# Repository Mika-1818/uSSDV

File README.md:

# uSSDV
µSSDV is a gps tracker and image transmission system built on the cheap esp32 cam module.
This is still work in progress and not tested yet. Expect to see some tests soon though.

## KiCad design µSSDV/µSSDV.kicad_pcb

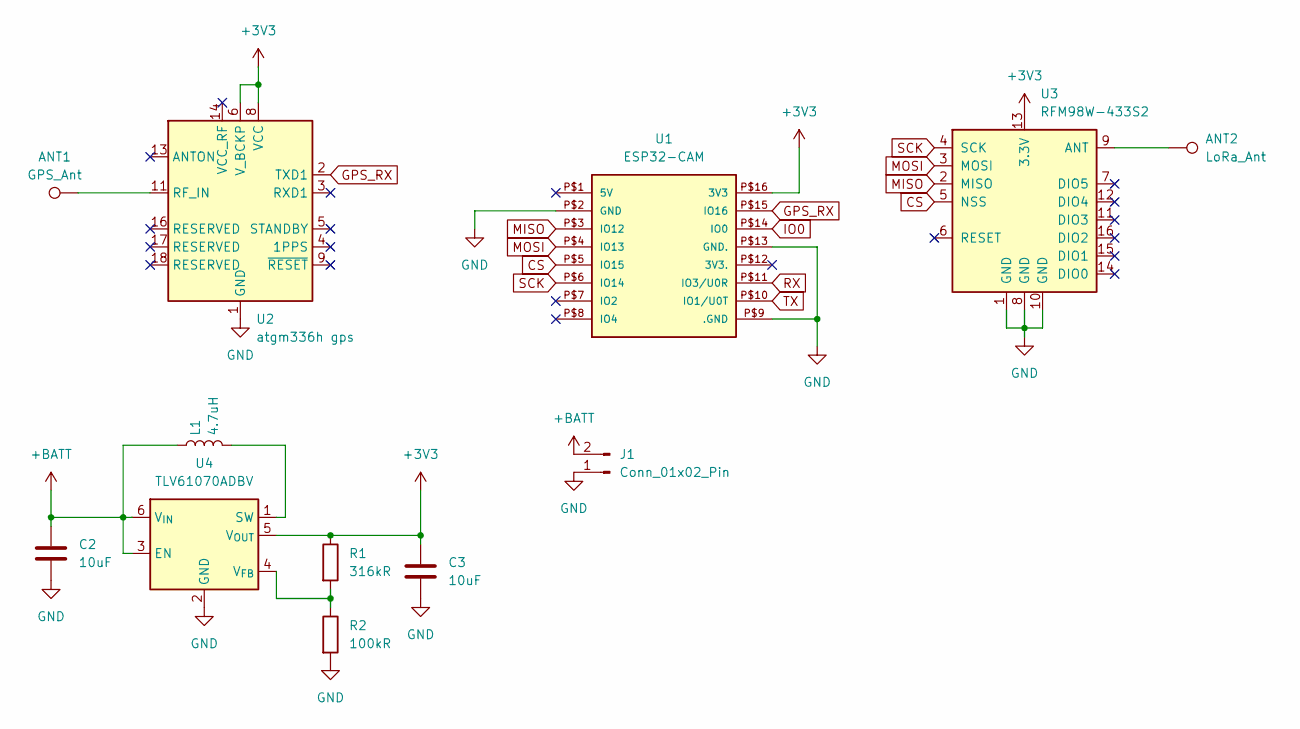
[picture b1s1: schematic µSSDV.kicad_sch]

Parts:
ANT1: GPS_Ant; PinHeader_1x01_P2.54mm_Vertical
ANT2: LoRa_Ant; PinHeader_1x01_P2.54mm_Vertical
C2, C3: 10uF; C_0603_1608Metric_Pad1.08x0.95mm_HandSolder
J1: Conn_01x02_Pin; PinHeader_1x02_P2.54mm_Vertical
L1: 4.7uH; L_Changjiang_FNR5040S
R1: 316kR; R_0603_1608Metric_Pad0.98x0.95mm_HandSolder
R2: 100kR; R_0603_1608Metric_Pad0.98x0.95mm_HandSolder
U1: ESP32-CAM
U2: atgm336h gps; Quectel_L70-R
U3: RFM98W-433S2; HOPERF_RFM9XW_SMD
U4: TLV61070ADBV; SOT-23-6_Handsoldering

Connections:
+3V3: C3.1, R1.1, U1.P$16 (3V3), U2.6 (V_BCKP), U2.8 (VCC), U3.13 (3.3V), U4.5 (V_{OUT})
+BATT: C2.1, J1.2, L1.1, U4.3 (EN), U4.6 (V_{IN})
CS: U1.P$5 (IO15), U3.5 (NSS)
GND: C2.2, C3.2, J1.1, R2.2, U1.P$2 (GND), U1.P$9 (.GND), U1.P$13 (GND.), U2.1 (GND), U2.10 (GND), U2.12 (GND), U3.1 (GND), U3.8 (GND), U3.10 (GND), U4.2 (GND)
GPS_RX: U1.P$15 (IO16), U2.2 (TXD1)
IO0: U1.P$14 (IO0)
MISO: U1.P$3 (IO12), U3.2 (MISO)
MOSI: U1.P$4 (IO13), U3.3 (MOSI)
unnamed: ANT1.1, U2.11 (RF_IN)
unnamed: ANT2.1, U3.9 (ANT)
unnamed: L1.2, U4.1 (SW)
unnamed: R1.2, R2.1, U4.4 (V_{FB})
RX: U1.P$11 (IO3/U0R)
SCK: U1.P$6 (IO14), U3.4 (SCK)
TX: U1.P$10 (IO1/U0T)

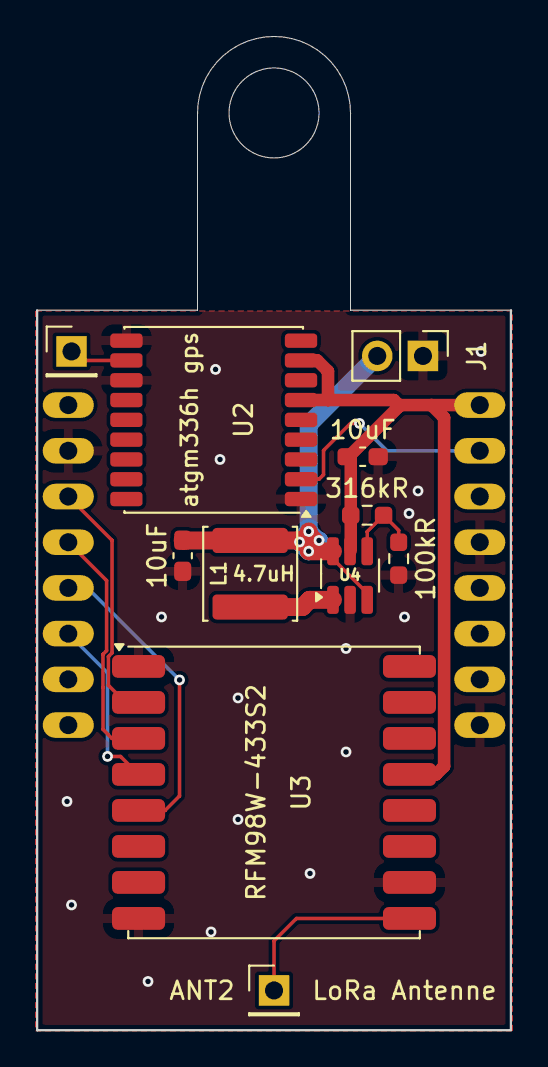
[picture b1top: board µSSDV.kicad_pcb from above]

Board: 2 copper layers, 26.3 x 55.2 mm, 12 parts (0 on the bottom side), 12 nets.

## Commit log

2025-11-26 Initial commit, pcb version 1.0
2025-12-01 Minor PCB updates
2025-12-10 small fix

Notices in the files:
µSSDV/µSSDV.kicad_pcb:
© Mika Köching
